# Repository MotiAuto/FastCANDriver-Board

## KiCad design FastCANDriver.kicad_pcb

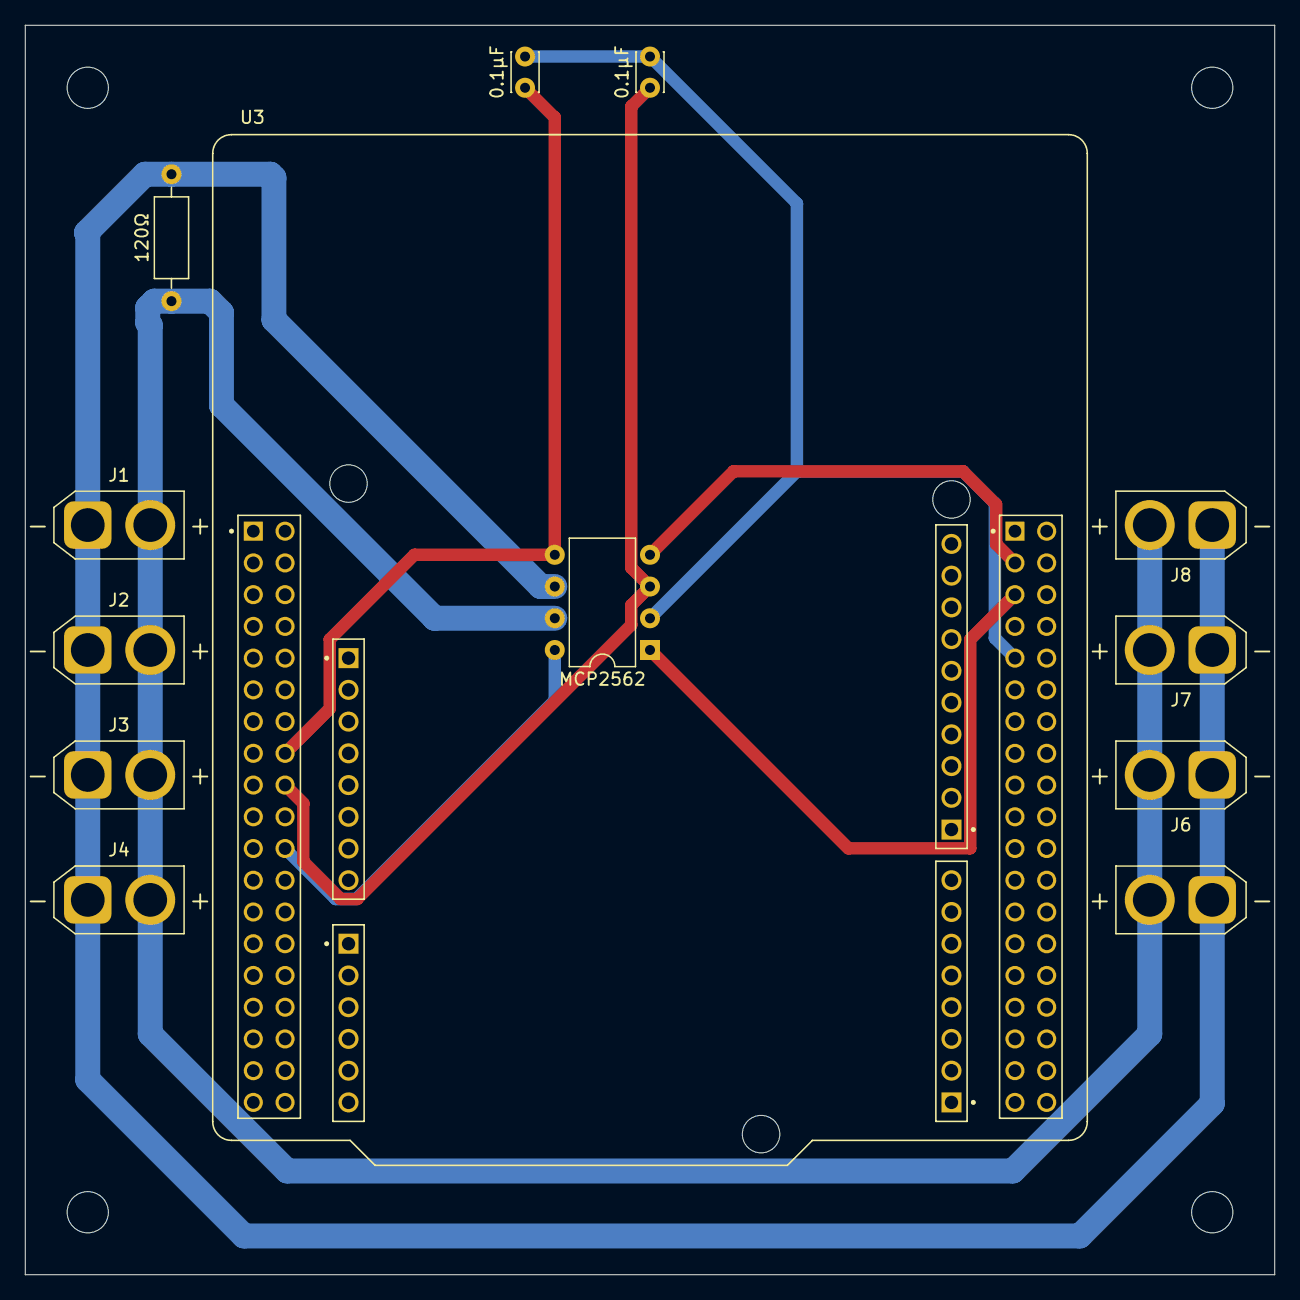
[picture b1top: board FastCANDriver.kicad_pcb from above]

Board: 2 copper layers, 100.0 x 100.0 mm, 13 parts (0 on the bottom side), 7 nets.

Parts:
0.1μF, 0.1μF#2: 0.1μ; C_Disc_D3.0mm_W2.0mm_P2.50mm
120Ω: 120; R_Axial_DIN0207_L6.3mm_D2.5mm_P10.16mm_Horizontal
J1: CAN_1; AMASS_XT30U-F_1x02_P5.0mm_Vertical
J2: CAN_2; AMASS_XT30U-F_1x02_P5.0mm_Vertical
J3: CAN_3; AMASS_XT30U-F_1x02_P5.0mm_Vertical
J4: CAN_4; AMASS_XT30U-F_1x02_P5.0mm_Vertical
J5: CAN_5; AMASS_XT30U-F_1x02_P5.0mm_Vertical
J6: CAN_6; AMASS_XT30U-F_1x02_P5.0mm_Vertical
J7: CAN_7; AMASS_XT30U-F_1x02_P5.0mm_Vertical
J8: CAN_8; AMASS_XT30U-F_1x02_P5.0mm_Vertical
MCP2562: MCP2562-E-P; DIP-8_W7.62mm
U3: NUCLEO-F446RE; MODULE_NUCLEO-F446RE

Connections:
3.3V: 0.1μF#2.1, MCP2562.5 (Vio), U3.CN7_16 (CN7_+3V3)
5V: 0.1μF.1, MCP2562.3 (VDD), U3.CN7_18 (CN7_+5V)
CAN_H: 120Ω.1, J1.2, J2.2, J3.2, J4.2, J5.2, J6.2, J7.2, J8.2, MCP2562.7 (CANH)
CAN_L: 120Ω.2, J1.1, J2.1, J3.1, J4.1, J5.1, J6.1, J7.1, J8.1, MCP2562.6 (CANL)
GND: 0.1μF.2, 0.1μF#2.2, MCP2562.2 (VSS), MCP2562.8 (STBY), U3.CN7_19 (CN7_GND__1), U3.CN7_20 (CN7_GND__2), U3.CN7_22 (CN7_GND__3), U3.CN10_9 (CN10_GND)
RX: MCP2562.4 (RXD), U3.CN10_3 (PB8)
TX: MCP2562.1 (TXD), U3.CN10_5 (PB9)
